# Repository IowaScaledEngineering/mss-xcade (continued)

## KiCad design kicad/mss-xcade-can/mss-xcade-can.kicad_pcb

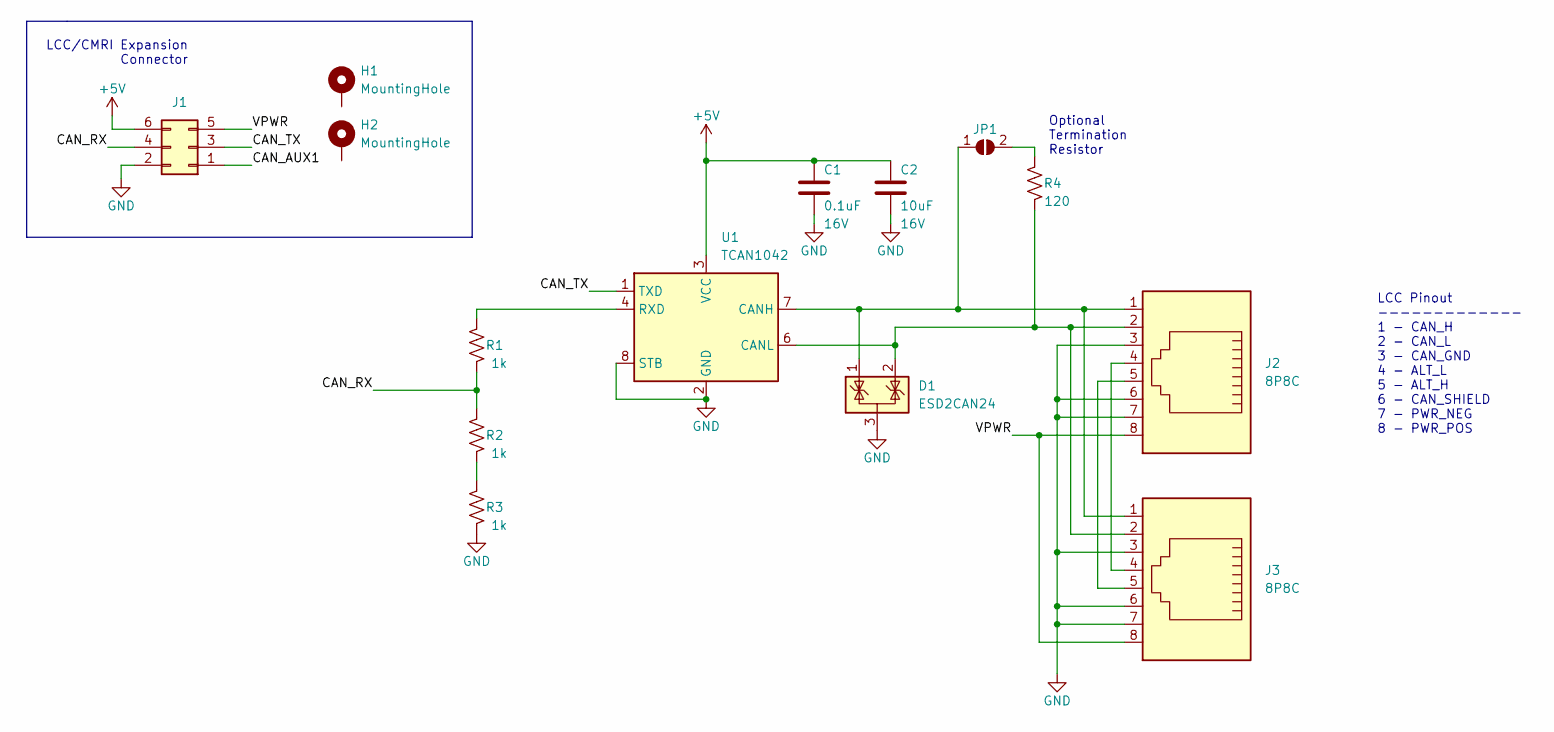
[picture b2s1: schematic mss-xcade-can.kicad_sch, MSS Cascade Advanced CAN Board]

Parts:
C1: 0.1uF; C_0805_2012Metric; Voltage 16V
C2: 10uF; C_0805_2012Metric; Voltage 16V
D1: ESD2CAN24; SOT-23
H1, H2: MountingHole; MountingHole_3.2mm_M3_ISO14580_Pad
J1: Conn_02x03_Odd_Even; PinHeader_2x03_P2.54mm_Vertical
J2, J3: 8P8C; RJ45_Amphenol_54602-x08_Horizontal
JP1: SolderJumper_2_Open; SolderJumper-2_P1.3mm_Open_RoundedPad1.0x1.5mm
R1, R2, R3: 1k; R_0805_2012Metric
R4: 120; R_0805_2012Metric
U1: TCAN1042; SOIC-8_3.9x4.9mm_P1.27mm

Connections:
+5V: C1.1, C2.1, J1.6, U1.3 (VCC)
/CAN_AUX1: J1.1
/CAN_RX: J1.4, R1.1, R2.2
/CAN_TX: J1.3, U1.1 (TXD)
/VPWR: J1.5, J2.8, J3.8
GND: C1.2, C2.2, D1.3 (A), J1.2, J2.3, J2.6, J2.7, J3.3, J3.6, J3.7, R3.1, U1.2 (GND), U1.8 (STB)
unnamed: D1.1 (K), J2.1, J3.1, JP1.1 (A), U1.7 (CANH)
unnamed: D1.2 (K), J2.2, J3.2, R4.1, U1.6 (CANL)
unnamed: J2.4, J3.4
unnamed: J2.5, J3.5
unnamed: JP1.2 (B), R4.2
unnamed: R1.2, U1.4 (RXD)
unnamed: R2.1, R3.2

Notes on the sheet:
LCC/CMRI Expansion Connector
Optional Termination Resistor
LCC Pinout ------------- 1 - CAN_H 2 - CAN_L 3 - CAN_GND 4 - ALT_L 5 - ALT_H 6 - CAN_SHIELD 7 - PWR_NEG 8 - PWR_POS

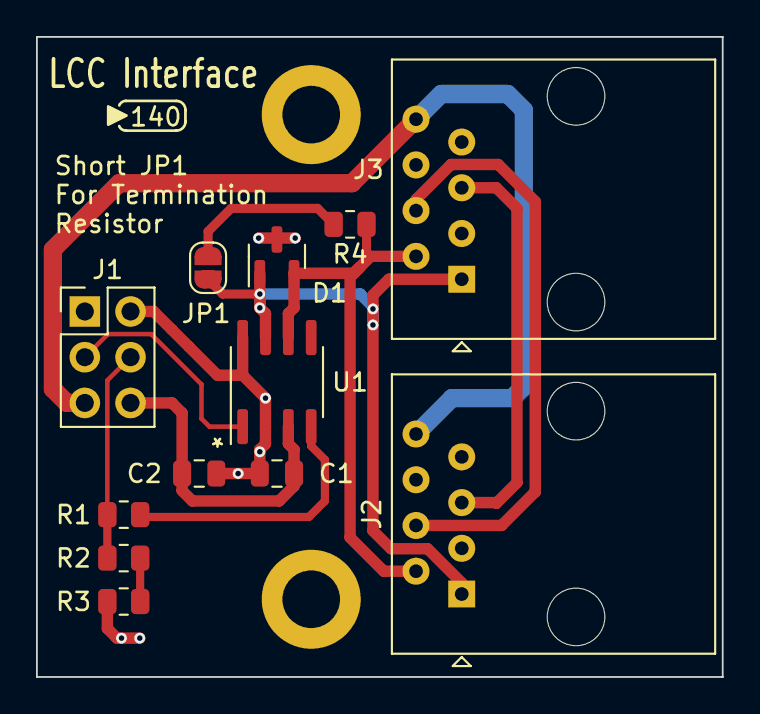
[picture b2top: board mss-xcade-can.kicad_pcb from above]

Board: 2 copper layers, 38.1 x 35.6 mm, 14 parts (0 on the bottom side), 12 nets.

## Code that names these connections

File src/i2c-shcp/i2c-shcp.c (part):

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//  Yellow address, bitmask
//  Green address, bitmask

#define SIGNAL_HEAD_0_DEF   &PORTD, _BV(PD0), &PORTD, _BV(PD1), &PORTD, _BV(PD2)
#define SIGNAL_HEAD_1_DEF   &PORTD, _BV(PD3), &PORTD, _BV(PD4), &PORTA, _BV(PA2)
#define SIGNAL_HEAD_2_DEF   &PORTA, _BV(PA3), &PORTB, _BV(PB6), &PORTB, _BV(PB7)
#define SIGNAL_HEAD_3_DEF   &PORTD, _BV(PD5), &PORTD, _BV(PD6), &PORTD, _BV(PD7)
#define SIGNAL_HEAD_4_DEF   &PORTB, _BV(PB0), &PORTB, _BV(PB1), &PORTB, _BV(PB2)
#define SIGNAL_HEAD_5_DEF   &PORTB, _BV(PB3), &PORTB, _BV(PB4), &PORTB, _BV(PB5)
#define SIGNAL_HEAD_6_DEF   &PORTC, _BV(PC7), &PORTA, _BV(PA1), &PORTC, _BV(PC0)
#define SIGNAL_HEAD_7_DEF   &PORTC, _BV(PC1), &PORTC, _BV(PC2), &PORTC, _BV(PC3)

#define SENSE_COMMON_ANODE 0x01

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	//  PA6 - n/a
	//  PA5 - n/a
	//  PA4 - n/a
	//  PA3 - Input  - B1 Signal - RED
	//  PA2 - Input  - A2 Signal - GREEN
	//  PA1 - Output - D1 Signal - YELLOW
	//  PA0 - Input  - Common anode / common cathode sense (1 = common anode)

	// PORT B
	//  PB7 - Output - B1 Signal - GREEN
	//  PB6 - Output - B1 Signal - YELLOW
	//  PB5 - Output - C2 Signal - GREEN
	//  PB4 - Output - C2 Signal - YELLOW
	//  PB3 - Output - C2 Signal - RED
	//  PB2 - Output - C1 Signal - GREEN
	//  PB1 - Output - C1 Signal - YELLOW
	//  PB0 - Output - C1 Signal - RED

	// PORT C
	//  PC7 - Output - D1 Signal - RED
	//  PC6 - n/a    - /RESET (not I/O pin)
	//  PC5 - n/a    - SCL
	//  PC4 - n/a    - SDA
	//  PC3 - Output - D2 Signal - GREEN
	//  PC2 - Output - D2 Signal - YELLOW
	//  PC1 - Output - D2 Signal - RED
	//  PC0 - Output - D1 Signal - GREEN

	// PORT D
	//  PD7 - Output - B2 Signal - GREEN
	//  PD6 - Output - B2 Signal - YELLOW
	//  PD5 - Output - B2 Signal - RED
	//  PD4 - Output - A2 Signal - YELLOW
	//  PD3 - Output - A2 Signal - RED
	//  PD2 - Output - A1 Signal - GREEN
	//  PD1 - Output - A1 Signal - YELLOW
	//  PD0 - Output - A1 Signal - RED


	PORTA = 0b00000001;
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
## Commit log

2024-08-11 Work in progress
2024-08-11 More updates
2024-08-29 Temporarily add the relay siding end thingy
2024-09-03 Add draft siding truth table to this directory for now - need to split the whole thing into its own project
2024-09-03 xcade upates
2024-11-26 Refactor signal drivers to their own schematic and add picoblade connectors
2025-03-03 First cut of xcade PCB
2025-03-29 Update expansion connector and add CAN interface module board
2025-04-04 Fix a DRC issue and add some more metal
2025-04-04 Add optional termination resistor
2025-04-18 Add signal head coprocessor code, updated to actual pinout
2025-04-18 Fix issue with pin mapping and DDR, update comments
2025-05-08 Fix issue with signal D1 not having green setup correctly
2025-05-14 Move some heavy processing outside the ISR to make I2C more responsive, hopefully
2025-05-21 Tada! Missing pg files
2025-08-10 Hardware test arduino sketch
2025-08-19 Fix anode/cathode text, update version number
2025-08-20 Add temp source files to ignore
2025-08-26 Add makefile and instructions for tiny48, since I built three with the wrong parts
2026-03-29 Remove duplicate const
2026-06-09 Allow SHCP to recover from I2C fault
2026-06-19 PG 1.1
